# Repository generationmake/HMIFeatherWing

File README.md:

# HMIFeatherWing
HMI FeatherWing with EA DOGM132-5 2.1" display and joystick compatible to Adafruit Feather

## PCB

### Top

### Bottom

## License

This hardware is licensed under the CERN OHL v. 1.2

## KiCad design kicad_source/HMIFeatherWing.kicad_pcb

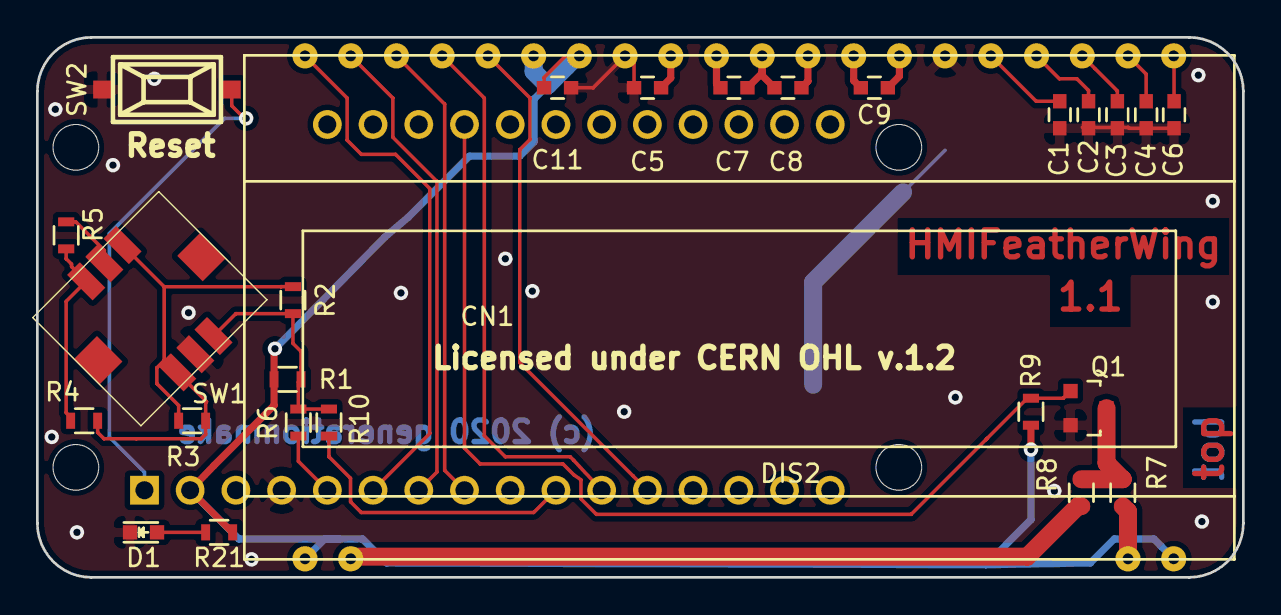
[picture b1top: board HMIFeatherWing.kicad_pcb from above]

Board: 2 copper layers, 67.0 x 30.0 mm, 27 parts (0 on the bottom side), 31 nets.

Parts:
C1, C2, C3, C4, C5, C6, C7, C8, C9, C11: 1uF; C_0603
CN1: ADAFRUIT_FEATHER; ADAFRUIT_FEATHER_HOLES
D1: green; LED_0603
DIS2: EA_DOGM132-5; EA_DOGM081_162_163_132
Q1: 2N7002; SOT-23
R1: 2k; R_0603
R2: 330; R_0603
R3: 620; R_0603
R4, R9, R21: 1k; R_0603
R5: 3k3; R_0603
R6: DNI; R_0603
R7, R8: 30; R_0603
R10: 0R; R_0603
SW1: ALPS_SKRH
SW2: SW_PUSH; smd_push

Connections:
+3V3: C11.1, CN1.2, DIS2.1, DIS2.20, DIS2.34, DIS2.35, R1.1, R9.1, R21.2
/BUTTON_DOWN: R3.2, R4.1, SW1.6
/BUTTON_LEFT: R4.2, R5.1, SW1.3
/BUTTON_SELECT: R5.2, SW1.2
/BUTTON_UP: R2.2, R3.1, SW1.1
/DISPLAY_BL: CN1.25, Q1.1, R9.2
/DIS_A0: CN1.8, DIS2.38
/DIS_C1: DIS2.2, R8.1
/DIS_C2: DIS2.19, R7.1
/DIS_CAP1N: C7.2, C8.1, DIS2.30
/DIS_CAP1P: C8.2, DIS2.29
/DIS_CAP2N: C9.2, DIS2.27
/DIS_CAP2P: C9.1, DIS2.28
/DIS_CAP3P: C7.1, DIS2.31
/DIS_CLK: CN1.11, DIS2.37
/DIS_CS: CN1.6, DIS2.40
/DIS_RESET: CN1.7, DIS2.39
/DIS_SI: CN1.12, DIS2.36
/DIS_V0: C6.1, DIS2.21
/DIS_V1: C4.1, DIS2.22
/DIS_V2: C3.1, DIS2.23
/DIS_V3: C2.1, DIS2.24
/DIS_V4: C1.1, DIS2.25
/DIS_VOUT: C5.1, DIS2.32
/KEYPAD_A0: R1.2, R2.1, R6.2, R10.2, SW1.4
/KEYPAD_A0_0: CN1.5, R6.1
/KEYPAD_A0_5: CN1.10, R10.1
/RESET: CN1.1, SW2.2
GND: C1.2, C2.2, C3.2, C4.2, C5.2, C6.2, C11.2, CN1.4, D1.1, DIS2.26, DIS2.33, Q1.2, SW1.5, SW2.1
unnamed: D1.2, R21.1
unnamed: Q1.3, R7.2, R8.2

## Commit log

2019-12-27 added kicad project files
2019-12-27 added license files
2019-12-27 updated Readme and added images
2019-12-27 corrected Readme
2020-01-24 started development for 1.1, made pads for ALPS SKRH a little bit longer

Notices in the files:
kicad_source/HMIFeatherWing.kicad_pcb:
Licensed under CERN OHL v.1.2
(c) 2020 generationmake
This documentation describes Open Hardware and is licensed
under the CERN OHL v. 1.2.
of the CERN OHL v.1.2. (http://ohwr.org/cernohl). This documentation
